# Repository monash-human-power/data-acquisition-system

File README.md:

T2 VCU Data Acquisition System
This repository contains the Raspberry Pi Vehicle Control Unit (VCU) software used by Monash Human Power T2.
The VCU currently performs two main tasks:
Reads vehicle sensor data.
Streams camera footage and telemetry to the rider phone.
The camera and telemetry pipelines are intentionally kept separate. SPI support has been added as an independent hardware communication layer and is used by the ADS131M08 strain gauge sensor.
---
Current System Architecture
```text

                         Raspberry Pi 5 VCU

                                |

              +-----------------+-----------------+

              |                                   |

              |                                   |

         Camera Pipeline                   Telemetry Pipeline

              |                                   |

         Camera.cpp                        VCUController

              |                                   |

         rpicam-vid                         SensorManager

              |                                   |

           FFmpeg                              Sensors

              |                                   |

          MediaMTX                         SensorReading

              |                                   |

            RTSP                           DataSerialiser

              |                                   |

              |                           CommunicationManager

              |                                   |

              +---------------+-------------------+

                              |

                         Ethernet link

                              |

                        Android Phone

```
The Raspberry Pi uses the fixed Ethernet address:
```text

10.55.0.1

```
The Android phone currently uses:
```text

10.55.0.2

```
---
Program Startup
The program begins in:
```text

src/main.cpp

```
`main.cpp` is responsible for starting the camera system and starting the main VCU controller.
The basic startup flow is:
```text

main()

 |

 +--> Register SIGINT handler

 |

 +--> Create Camera

 |

 +--> Camera::startStream()

 |

 +--> Create VCUController

 |

 +--> VCUController::run()

```
The camera and sensor systems then run alongside each other.
Pressing:
```text

Ctrl+C

```
stops the camera stream before the VCU exits.
---
Camera Pipeline
The camera system is intentionally separate from the sensor telemetry system.
The current pipeline is:
```text

Pi Camera

   |

   v

Camera.cpp

   |

   v

rpicam-vid

   |

   v

FFmpeg

   |

   v

MediaMTX

   |

   v

RTSP

   |

   v

Android Phone

```
The current camera stream is available at:
```text

rtsp://10.55.0.1:8554/cam1

```
The camera implementation is contained in:
```text

src/sensors/Camera.h

src/sensors/Camera.cpp

```
Changes to telemetry should not require changes to the camera pipeline.
---
VCU Controller
The main VCU logic is handled by:
```text

src/core/VCUController.h

src/core/VCUController.cpp

```
When `VCUController::run()` starts, it first calls:
```cpp

setup();

```
The setup process currently:
```text

Initialise CommunicationManager

        |

        v

Create I2C bus

/dev/i2c-1

        |

        v

Create GyroscopeSensor

        |

        v

Add sensor to SensorManager

        |

        v

Initialise sensors

        |

        v

Calibrate gyroscope

        |

        v

Start main VCU loop

```
---
Main Sensor Loop
Once setup has completed, the VCU continuously performs:
```text

SensorManager::readAll()

        |

        v

SensorManager::getReadings()

        |

        v

vector<SensorReading>

        |

        v

DataSerialiser::toJSON()

        |

        v

vector<string>

        |

        v

CommunicationManager::sendMessages()

        |

        v

Phone

```
The loop then sleeps according to:
```cpp

config.getSensorReadIntervalMs()

```
before reading the sensors again.
The high-level loop is:
```cpp

while (running)

{

    sensorManager.readAll();

    std::vector<SensorReading> readings =

        sensorManager.getReadings();

    std::vector<std::string> messages =

        DataSerialiser::toJSON(readings);

    communicationManager.sendMessages(messages);

    // Wait until next sensor sample

}

```
---
Sensors
All sensors inherit from:
```text

SensorBase

```
defined in:
```text

src/sensors/Sensor.h

```
A sensor is responsible for:
```text

Initialising hardware

Reading hardware

Updating its SensorReading

```
A sensor should NOT be responsible for:
```text

JSON formatting

TCP networking

Phone communication

```
Those responsibilities belong to `DataSerialiser` and `CommunicationManager`.
---
SensorReading
Sensor data is passed through the system using:
```text

src/data/SensorReading.h

```
The current generic structure is:
```cpp

struct SensorReading

{

    std::string sensorID;

    std::uint64_t timestamp;

    std::unordered_map<std::string, float> values;

    bool isValid;

};

```
The `values` map allows different sensors to provide different measurements without changing the common VCU architecture.
For example, the gyroscope currently produces:
```text

accel_x

accel_y

accel_z

gyro_x

gyro_y

gyro_z

temperature_c

```
A future wheel-speed sensor could simply provide:
```text

speed_kmh

```
without requiring a different `SensorReading` structure.
---
Gyroscope
The currently implemented sensor is an MPU6050.
Files:
```text

src/sensors/GyroscopeSensor.h

src/sensors/GyroscopeSensor.cpp

```
It is currently connected directly to:
```text

/dev/i2c-1

```
with I2C address:
```text

0x68

```
The sensor reads:
```text

Accelerometer X

Accelerometer Y

Accelerometer Z

Gyroscope X

Gyroscope Y

Gyroscope Z

Temperature

```
During VCU startup, the gyroscope is calibrated.
The bike/gyro should remain still while the following message is displayed:
```text

Keep gyroscope still for calibration...

```
---
SensorManager
Files:
```text

src/core/SensorManager.h

src/core/SensorManager.cpp

```
`SensorManager` owns the collection of sensors.
Its main responsibilities are:
```text

addSensor()

initAll()

readAll()

getReadings()

getSensorCount()

```
`readAll()` asks every registered sensor to update its latest reading.
`getReadings()` then collects the latest `SensorReading` from every sensor.
This means additional sensors should generally only need to:
Implement the `SensorBase` interface.
Be added to `SensorManager` during VCU setup.
---
DataSerialiser
Files:
```text

src/data/DataSerialiser.h

src/data/DataSerialiser.cpp

```
`DataSerialiser` is responsible for converting `SensorReading` objects into JSON.
Sensors should not manually create JSON.
Example gyroscope packet:
```json

{

  "sensor": "gyro_1",

  "timestamp": 1791119904187,

  "values": {

    "temperature_c": 18.2506,

    "gyro_z": -0.106794,

    "gyro_y": 0.194046,

    "accel_z": 0.506104,

    "gyro_x": -0.0588548,

    "accel_y": 0.377686,

    "accel_x": -0.753418

  },

  "valid": true

}

```
The order of entries inside `values` should not be relied upon.
JSON object field order is not significant.
---
CommunicationManager
Files:
```text

src/communication/CommunicationManager.h

src/communication/CommunicationManager.cpp

```
`CommunicationManager` handles communication between the VCU and phone.
The current telemetry system runs a TCP server on:
```text

10.55.0.1:9001

```
The phone acts as the TCP client.
The data path is:
```text

VCU

 |

 | JSON over TCP

 v

10.55.0.1:9001

 |

 | Ethernet

 v

Android Phone

```
Each telemetry message is sent as JSON.
The telemetry connection is separate from the RTSP camera connection.
Therefore the phone receives:
```text

Camera:

rtsp://10.55.0.1:8554/cam1

Telemetry:

TCP 10.55.0.1:9001

```
---
Testing Telemetry Locally
Start the VCU:
```bash

./vcu

```
The output should include:
```text

Telemetry server ready on port 9001

Phone should connect to 10.55.0.1:9001

```
In another terminal on the Pi, connect using netcat:
```bash

nc 127.0.0.1 9001

```
You should receive JSON packets such as:
```json

{"sensor":"gyro_1","timestamp":1791119904187,"values":{"temperature_c":18.2506,"gyro_z":-0.106794,"gyro_y":0.194046,"accel_z":0.506104,"gyro_x":-0.0588548,"accel_y":0.377686,"accel_x":-0.753418},"valid":true}

```
Press:
```text

Ctrl+C

```
to exit netcat.
---
SPI Communication (New — Hardware Layer)
The VCU now includes a reusable SPI bus implementation in addition to the existing I2C bus. It is used by the ADS131M08 strain gauge sensor described below.
Files
```text
src/hardware/SPIBus.h
src/hardware/SPIBus.cpp
tests/test_spi.cpp
```
`SPIBus` functionality
`openBus()` — opens a Linux `spidev` device and configures its SPI mode, bits per word and clock speed.
`closeBus()` — closes the file descriptor.
`transfer(tx, rx)` — performs a full-duplex SPI transfer: transmit and receive happen together.
`write(data)` — sends bytes while discarding received bytes.
`isOpen()` — reports whether the device is open.
The default constructor settings are:
```cpp
SPIBus spi("/dev/spidev0.0", 1000000, 0);
```
These specify device `/dev/spidev0.0`, a 1 MHz clock, and SPI mode 0. Settings may need changing for a particular sensor. The Linux SPI interface is accessed through `ioctl()` and `<linux/spi/spidev.h>`.
Compile SPI test
From the repository root, on Linux or WSL with the Linux SPI headers available:
```bash
g++ -std=c++17 tests/test_spi.cpp src/hardware/SPIBus.cpp -Isrc -o test_spi
```
Run the test on a Raspberry Pi with SPI enabled:
```bash
./test_spi
```
To check whether a Raspberry Pi exposes SPI devices:
```bash
ls /dev/spidev*
```
If needed, enable SPI under `sudo raspi-config` → Interface Options → SPI. Device names may vary with configuration.
Test status: The SPI code has been compiled with C++17 in WSL. A successful compile confirms source-level buildability, not successful communication with an SPI peripheral. WSL usually has no `/dev/spidev0.0`, and even a successful transfer on a Pi without a connected peripheral does not validate sensor data.
Adding SPI sensors
SPI sensors inherit from `SPISensor` (`src/sensors/SPISensor.h`), which holds a reference to a shared `SPIBus`. Implement a sensor-specific driver that writes a `SensorReading` and register it with `SensorManager` during `VCUController::setup()`. The existing `DataSerialiser` → `CommunicationManager` → phone telemetry path should remain unchanged. The camera pipeline is also unaffected.
`openBus()`, `transfer()` and `isOpen()` are virtual so that tests can replace the bus with a simulated device.
---
Strain Gauges (ADS131M08 over SPI)
Full Wheatstone bridge strain gauges are read through a TI ADS131M08 8-channel, 24-bit ADC.
Files
```text
src/hardware/ADS131M08.h
src/hardware/ADS131M08.cpp
src/hardware/GPIOInput.h
src/hardware/GPIOInput.cpp
src/sensors/SPISensor.h
src/sensors/SPISensor.cpp
src/sensors/analog/StrainGaugeSensor.h
src/sensors/analog/StrainGaugeSensor.cpp
tests/test_strain_gauge.cpp
```
`ADS131M08` is the chip driver: frame building, RESET/RREG/WREG/NULL commands, PGA gain, oversampling ratio, global chop and output CRC checking. `StrainGaugeSensor` turns bridge voltages into strain. `GPIOInput` watches the ADC's DRDY pin for falling edges using the Linux GPIO character device (`/dev/gpiochipN`), so no extra library is needed.
SPI settings
The ADS131M08 uses SPI mode 1 (CPOL = 0, CPHA = 1), not the `SPIBus` default of mode 0. `VCUController` opens `/dev/spidev0.0` at 1 MHz in mode 1 (see `SystemConfig`). Frames are 10 words of 24 bits (30 bytes): a response word, eight channel words and a CRC word.
Hardware requirements
CLKIN is driven by the on-board SiT1602BC-21-25E-4.096000G oscillator (4.096 MHz, 2.5 V). This frequency is set by `StrainGaugeADCSettings::clockHz`, so change it there if the oscillator changes. The output data rate is (CLKIN / 2) / OSR:
```text
OSR     Data rate at 4.096 MHz
1024    2000 SPS
2048    1000 SPS
4096     500 SPS   (default)
8192     250 SPS
16256    126 SPS
```
The datasheet specifies low-power mode (CLOCK PWR = 01) at a 4.096 MHz CLKIN, so that is the default (`StrainGaugeADCSettings::powerMode`). The crystal oscillator circuit is turned off (XTAL_DIS) because CLKIN is driven by the external oscillator. With the default 8 samples per reading, each `read()` takes about 16 ms. The SYNC/RESET pin must be held high. If CLKIN is missing, the ADC still answers commands but never produces data, and initialisation fails with `timed out waiting for ADS131M08 data (check CLKIN)`.
Voltage reference
AVDD and DVDD are both 3.3 V. The ADS131M08 has no AVSS pin: AGND (0 V) is its negative supply. REFIN is driven to 1.25 V by a 10k/10k divider (R9/R12) from the 2.5 V rail, so the driver sets EXTREF_EN (CLOCK bit 6) to use it as the reference. The ADC then uses 0.96 × REFIN = 1.2 V, which gives a full-scale range of ±1.2 V / gain. These are the defaults in `StrainGaugeADCSettings` (`externalReference`, `refinVolts`).
EXTREF_EN is defined in the CLOCK register description (datasheet Table 8-17), although the summary register map (Table 8-12) shows it as reserved. The driver therefore reads CLOCK back. If the bit did not set, it prints `warning: EXTREF_EN did not set, using the internal 1.2 V reference`. Readings are still correct in that case, but no longer ratiometric. The startup line says which reference is in use.
The bridges are excited from the same 2.5 V rail, so the measurement is ratiometric: a low or noisy rail scales the bridge output and the reference together, so the strain value is unaffected.
Wiring to the Pi (via the VCU HAT)
The strain gauge board's J3 connects to J8 on the VCU HAT, which sits on the Pi's GPIO header. The HAT passes SCLK, MOSI, MISO and the chip selects through an ISO7761 digital isolator. The cable must be wired pin 1 to pin 1.
```text
ADC board J3   HAT J8      Path on the HAT              Pi 5 header
1  3.3 V       1  3V3      HAT 3V3 rail                 -
2  GND         2  GND      GND                          GND
3  SCLK        3  ISO-SCLK ISO7761 OUTC <- INC          pin 23 (GPIO 11)
4  DIN         4  ISO-MOSI ISO7761 OUTD <- IND          pin 19 (GPIO 10)
5  DOUT        5  ISO-MISO ISO7761 INF  -> OUTF         pin 21 (GPIO 9)
6  CS          6  ISO-CE0  ISO7761 OUTB <- INB          pin 24 (GPIO 8, CE0) -> /dev/spidev0.0
7  DRDY        7  ISO-INT0 (not through the isolator)   pin 18 (GPIO 24)
8  GND         8  GND      GND                          GND
```
ISO-CE0 has a 10k pull-up (R20), so the ADC stays deselected while the Pi is booting. HAT connector J9 is the same but uses CE1 (`/dev/spidev0.1`) and INT1 on pin 22 (GPIO 25), for a second SPI board.
DRDY
The ADC pulls DRDY low when a new conversion is ready, and DRDY falls again for every conversion even if the last one was not read. The ADC also buffers two samples per channel, so after the gap between VCU loop iterations both are full and old (datasheet 8.5.1.9.1). Each `read()` therefore drops stale DRDY edges, reads two frames to empty the buffer, and then, for each sample, waits for a falling edge on GPIO 24 and reads one SPI frame. Reading straight after DRDY falls also avoids reading while a conversion completes, which the datasheet warns blocks the next DRDY pulse. The GPIO is found by its chip label (`pinctrl-rp1` on the Pi 5) rather than a fixed `/dev/gpiochipN` path, because the number differs between kernel versions. Both the label and the line are set in `SystemConfig`.
If the GPIO cannot be opened, the sensor prints `warning: DRDY pin unavailable, polling STATUS instead` and keeps working by polling the STATUS register over SPI. The user running `./vcu` must be in the `gpio` group (and the `spi` group for `/dev/spidev0.0`), which the default Pi OS user already is. To check the pin from the shell, run `gpioinfo | grep -A30 pinctrl-rp1` (from the `gpiod` package) and look for line 24.
The isolator adds a delay to each signal, and MISO pays it twice: the clock goes out through the isolator and the data comes back through it. This has no effect at the default 1 MHz SCLK, but keep it in mind before raising `spiSpeedHz` far.
SYNC/RESET is pulled up to 3.3 V on the board through R19.
Hardware checks against the datasheet (SBAS950B, `adc_datasheet.pdf`)
- CLKIN level (out of spec): CLKIN is a digital input with VIH = 0.8 × DVDD = 2.64 V at DVDD = 3.3 V. The SiT1602BC-21-25E oscillator runs from 2.5 V, so its high level is at most 2.5 V. It may work on the bench, but it is below the guaranteed threshold. Use the 3.3 V version (SiT1602BC-21-33E-4.096000G) or power the oscillator from 3.3 V if the part allows it.
- Input voltage range: at gains of 8 to 128, each input must stay between AGND − 1.3 V and AVDD − 1.8 V (1.5 V at AVDD = 3.3 V). A bridge excited at 2.5 V sits at about 1.25 V, which is within range. A bridge excited at 3.3 V (about 1.65 V) would not be.
- REFIN: 1.1 V to 1.3 V, nominal 1.25 V. The full-scale range keeps the 1.2 : 1.25 ratio, which is the 0.96 factor used in the code.
- CLKIN frequency: 0.3 to 4.15 MHz in low-power mode, so 4.096 MHz is within range.
- CAP 220 nF, AVDD and DVDD 1 µF: matches the strain gauge board.
Raspberry Pi 5 setup
Enable SPI with `sudo raspi-config` → Interface Options → SPI, or add `dtparam=spi=on` to `/boot/firmware/config.txt`, then reboot. Check that `/dev/spidev0.0` exists (`ls /dev/spidev*`). This is SPI0 with chip select CE0, which the HAT routes to J8. If the strain gauge board is moved to J9 (CE1), change `spiDevicePath` in `SystemConfig` to `/dev/spidev0.1`.
Channel configuration
Each bridge is described by a `StrainChannelConfig`:
```cpp
StrainChannelConfig bridge0;
bridge0.name = "strain_0";        // telemetry key prefix
bridge0.channel = 0;              // AIN0P / AIN0N
bridge0.gaugeFactor = 2.1f;       // value on the gauge packet (spec 2.0-2.2)
bridge0.bridgeFactor = 1.0f;      // 1.0 for 4 active gauges
bridge0.excitationVoltage = 2.5f; // bridge excitation (2.5 V rail)
bridge0.pgaGain = 32;             // input range +/- 1.2 V / gain
```
Strain is calculated as:
```text
strain = (Vout - Vout_at_tare) / Vex / (gaugeFactor * bridgeFactor)
```
Use `bridgeFactor = (1 + poisson) / 2` for a full bridge with two axial and two Poisson gauges. A negative `bridgeFactor` flips the sign if the bridge is wired the other way round.
Choose the PGA gain so the largest expected bridge output, plus any bridge imbalance, stays inside +/- 1.2 V / gain. For example, 1000 microstrain with GF 2.0 and 2.5 V excitation gives 5 mV, which fits at gain 64 (+/- 18.75 mV) or gain 128 (+/- 9.375 mV).
Up to eight bridges can be read by one sensor by passing several `StrainChannelConfig` entries.
Startup and readings
During `VCUController::setup()` the sensor resets the ADC, checks the ID register, configures it, and then tares. The structure must be unloaded while this message is displayed:
```text
Keep strain gauges unloaded for taring...
```
Each `read()` averages 8 fresh conversions per channel and produces, for each bridge:
```text
<name>_microstrain
<name>_mv           raw bridge output before taring
```
Example packet:
```json
{"sensor":"strain_1","timestamp":1791119904187,"values":{"strain_0_microstrain":512.4,"strain_0_mv":4.62},"valid":true}
```
Settings shared by all channels (oversampling, samples per reading, global chop, clock frequency and reference) are passed as a `StrainGaugeADCSettings`, whose defaults match the strain gauge PCB.
`valid` is false if any configured input is saturated. If that happens, lower the PGA gain.
Strain gauge test
`tests/test_strain_gauge.cpp` checks the driver and strain maths against a simulated ADS131M08, so it runs on any Linux machine without hardware:
```bash
g++ -std=c++17 tests/test_strain_gauge.cpp src/hardware/SPIBus.cpp src/hardware/GPIOInput.cpp src/hardware/ADS131M08.cpp src/sensors/SPISensor.cpp src/sensors/analog/StrainGaugeSensor.cpp -Isrc -Isrc/hardware -Isrc/sensors -Isrc/sensors/analog -o test_strain_gauge
./test_strain_gauge
```
Test status: the strain gauge code passes the simulated-device test but has not yet been run against a real ADS131M08.
---
Adding a New Sensor
When adding another sensor, preserve the current architecture:
```text

Hardware

   |

   v

Sensor subclass

   |

   v

SensorReading

   |

   v

SensorManager

   |

   v

DataSerialiser

   |

   v

CommunicationManager

   |

   v

Phone

```
A new sensor should:
Inherit from `SensorBase` or the appropriate sensor subclass.
Implement `init()`.
Implement `read()`.
Store measurements inside `lastReading.values`.
Set `lastReading.timestamp`.
Set `lastReading.isValid`.
Be registered with `SensorManager`.
Do not add networking code directly to a sensor.
Do not add JSON formatting directly to a sensor.
---
Source Structure
```text

src/

├── communication/

│   ├── CommunicationManager.cpp

│   └── CommunicationManager.h

│

├── config/

│   ├── SystemConfig.cpp

│   └── SystemConfig.h

│

├── core/

│   ├── SensorManager.cpp

│   ├── SensorManager.h

│   ├── VCUController.cpp

│   └── VCUController.h

│

├── data/

│   ├── DataSerialiser.cpp

│   ├── DataSerialiser.h

│   ├── SensorReading.cpp

│   └── SensorReading.h

│

├── hardware/

│   ├── ADS131M08.cpp
│   ├── ADS131M08.h
│   ├── I2CBus.cpp

│   ├── I2CBus.h
│   ├── SPIBus.cpp
│   └── SPIBus.h

│

├── sensors/

│   ├── Camera.cpp

│   ├── Camera.h

│   ├── GyroscopeSensor.cpp

│   ├── GyroscopeSensor.h

│   ├── I2CSensor.cpp

│   ├── I2CSensor.h

│   ├── Sensor.h

│   └── ...

│

└── main.cpp

```
---
Building the VCU
From the repository root:
```bash

g++ -std=c++17 src/main.cpp src/core/VCUController.cpp src/core/SensorManager.cpp src/config/SystemConfig.cpp src/communication/CommunicationManager.cpp src/data/DataSerialiser.cpp src/data/SensorReading.cpp src/hardware/I2CBus.cpp src/hardware/SPIBus.cpp src/hardware/GPIOInput.cpp src/hardware/ADS131M08.cpp src/sensors/I2CSensor.cpp src/sensors/SPISensor.cpp src/sensors/GyroscopeSensor.cpp src/sensors/analog/StrainGaugeSensor.cpp src/sensors/Camera.cpp -I. -Isrc -Isrc/core -Isrc/config -Isrc/communication -Isrc/data -Isrc/hardware -Isrc/sensors -Isrc/sensors/i2c -Isrc/sensors/analog -Isrc/util -pthread -o vcu

```
Run with:
```bash

./vcu

```
Stop with:
```text

Ctrl+C

```

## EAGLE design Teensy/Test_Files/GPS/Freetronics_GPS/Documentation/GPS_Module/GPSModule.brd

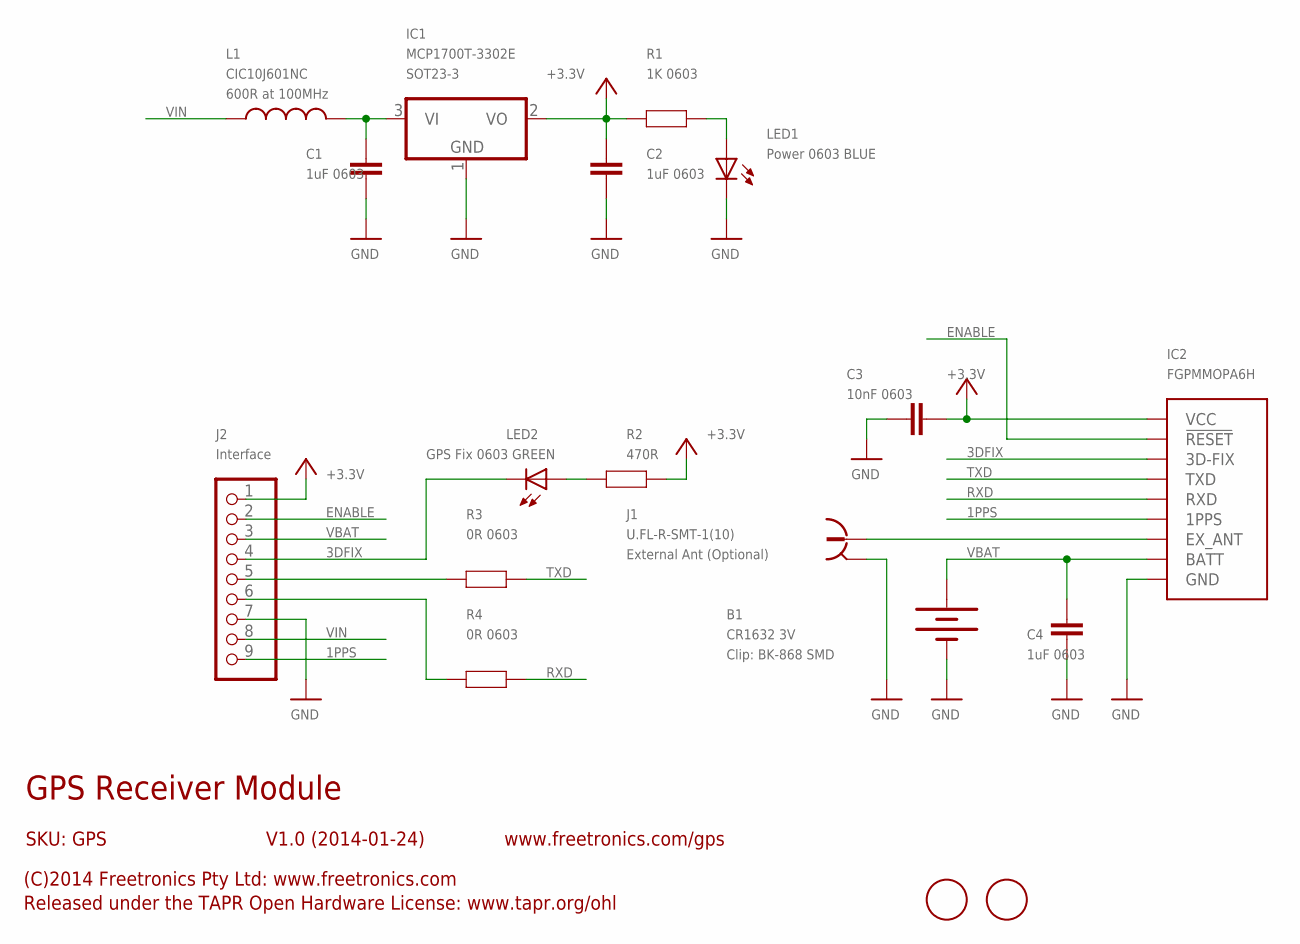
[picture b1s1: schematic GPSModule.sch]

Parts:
B1: CR1632 3V; BATCON_16MM
C1, C2, C4: 1uF 0603; 0603
C3: 10nF 0603; 0603
FD1, FD2: FIDUCIAL; FIDUCIAL_1MM
IC1: MCP1700T-3302E; SOT23
IC2: FGPMMOPA6H; GPS
J1: U.FL-R-SMT-1(10); UFL
J2: Interface; 1X09
L1: 600R at 100MHz; 0603
LED1: Power 0603 BLUE; LED-0603
LED2: GPS Fix 0603 GREEN; LED-0603
R1: 1K 0603; 0603
R2: 470R; 0603
R3, R4: 0R 0603; 0603

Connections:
1PPS: IC2.13 (1PPS), J2.9
3DFIX: IC2.5 (3D-FIX), J2.4, LED2.C
+3V3: C2.2, C3.1, IC1.2 (VO), IC2.1 (VCC), J2.1, R1.2, R2.1
ENABLE: IC2.2 (!RESET), J2.2
GND: B1.GND (-), C1.1, C2.1, C3.2, C4.1, IC1.1 (GND), IC2.3 (GND), IC2.8 (GND), IC2.12 (GND), IC2.19 (GND), J1.GND, J1.GND@1 (GND), J2.7, LED1.C
unnamed: J2.5, R3.2
unnamed: IC2.11 (EX_ANT), J1.SIG
unnamed: LED1.A, R1.1
unnamed: LED2.A, R2.2
unnamed: C1.2, IC1.3 (VI), L1.2
unnamed: J2.6, R4.2
RXD: IC2.10 (RXD), R4.1
TXD: IC2.9 (TXD), R3.1
VBAT: B1.PWR@1 (+), C4.2, IC2.4 (BATT), J2.3
VIN: J2.8, L1.1

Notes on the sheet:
GPS Receiver Module
V1.0 (2014-01-24)
SKU: GPS
(C)2014 Freetronics Pty Ltd: www.freetronics.com
Released under the TAPR Open Hardware License: www.tapr.org/ohl
www.freetronics.com/gps

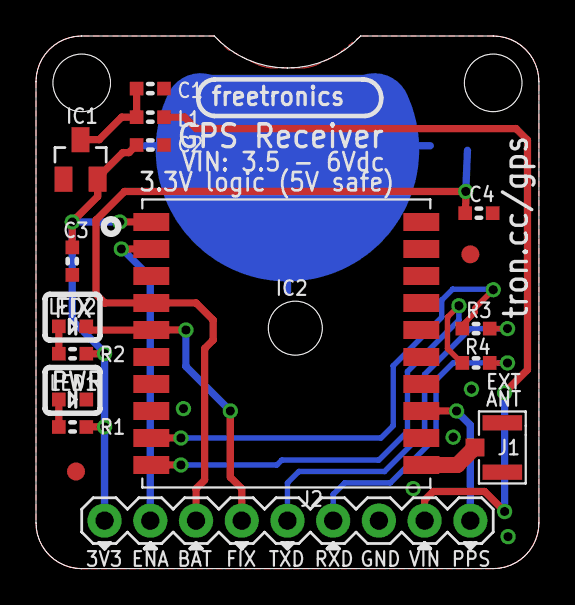
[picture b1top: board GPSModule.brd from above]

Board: 2 copper layers, 27.9 x 29.6 mm, 18 parts (1 on the bottom side), 15 nets.

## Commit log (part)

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2022-01-31 Add ant-plus service
2022-01-31 Update READMEs
2022-02-01 Add python-dotenv dependency
2022-02-02 Add ANT+ service (#83)
2022-02-06 Bump lodash from 4.17.19 to 4.17.21 in /ant_plus_sensor (#74)
2022-02-06 Bump numpy from 1.18.4 to 1.21.0 in /utils
    Bumps [numpy](https://github.com/numpy/numpy) from 1.18.4 to 1.21.0.
    - [Release notes](https://github.com/numpy/numpy/releases)
    - [Changelog](https://github.com/numpy/numpy/blob/main/doc/HOWTO_RELEASE.rst.txt)
    - [Commits](https://github.com/numpy/numpy/compare/v1.18.4...v1.21.0)
    ---
    updated-dependencies:
2022-02-06 Add .env.example file
2022-02-06 Fix file directory name in install script
2022-02-11 Document ant+ permissions requirements
2022-03-06 Update fake WM script to use Wm online status topic
2022-03-30 update: readme
2022-04-03 docs: simplify DAS readme
    - add table of contents
    - simplify install to 2 commands and a single command to run tests
2022-04-06 fix: remove old travis file
    This file is no longer needed as travis is not used as a CICD platform, GitHub actions are.
2022-04-06 Bump ajv from 6.10.2 to 6.12.6 in /ant_plus_sensor (#89)
    Bumps [ajv](https://github.com/ajv-validator/ajv) from 6.10.2 to 6.12.6.
    - [Release notes](https://github.com/ajv-validator/ajv/releases)
    - [Commits](https://github.com/ajv-validator/ajv/compare/v6.10.2...v6.12.6)
    ---
    updated-dependencies:
    - dependency-name: ajv
2022-04-06 docs: simplify DAS readme (#93)
    * docs: simplify DAS readme
    - add table of contents
    - simplify install to 2 commands and a single command to run tests
    * docs: add optional `poetry shell`
2022-04-06 feat: add dev container
2022-04-07 Fix speed sensor not getting detected
2022-04-07 Connect/read ant plus speed sensor (untested)
2022-04-07 Disable reed switch on back WM
2022-04-12 Wait before starting ant+ service
2022-04-13 fix: change logger to mqtt-logger package
2022-04-13 add mqtt-logger package
2022-04-13 refactor: format `das_data_generator`
2022-04-13 Use 'voltage' keyword for battery topic
2022-04-14 Add systemd servicee file for raw MQTT logger
2022-05-17 fix: do not write out excel tabs if no data is found (#100)
2022-05-18 Bump lodash from 4.17.19 to 4.17.21 in /ant_plus_sensor (#97)
    Bumps [lodash](https://github.com/lodash/lodash) from 4.17.19 to 4.17.21.
    - [Release notes](https://github.com/lodash/lodash/releases)
    - [Commits](https://github.com/lodash/lodash/compare/4.17.19...4.17.21)
    ---
    updated-dependencies:
    - dependency-name: lodash
2022-06-22 Bump numpy from 1.21.0 to 1.22.0 in /utils
    Bumps [numpy](https://github.com/numpy/numpy) from 1.21.0 to 1.22.0.
    - [Release notes](https://github.com/numpy/numpy/releases)
    - [Changelog](https://github.com/numpy/numpy/blob/main/doc/HOWTO_RELEASE.rst)
    - [Commits](https://github.com/numpy/numpy/compare/v1.21.0...v1.22.0)
    ---
    updated-dependencies:
2022-08-09 Implement v3 start topic in wireless modules (untested).
2022-08-22 add basic crash detection functions to mpu_sensor.py
2022-08-22 Remove redundant lines of code
2022-09-04 Remove redundant output statement
2022-09-06 Bump numpy from 1.21.0 to 1.22.0 in /utils (#102)
    Bumps [numpy](https://github.com/numpy/numpy) from 1.21.0 to 1.22.0.
    - [Release notes](https://github.com/numpy/numpy/releases)
    - [Changelog](https://github.com/numpy/numpy/blob/main/doc/HOWTO_RELEASE.rst)
    - [Commits](https://github.com/numpy/numpy/compare/v1.21.0...v1.22.0)
    ---
    updated-dependencies:
2022-09-15 add crash alert system
2022-09-17 Change LED mode depending on start message value
2022-09-26 add base class for raspberry pi based sensor
2022-09-26 add class for raspberry pi based wireless module
2022-09-27 update poetry files
2022-09-27 fix issues with mqtt
2022-09-27 move message sending files to a separate package
2022-09-27 add slack webhook parameter to class calls
2022-10-04 add some documentation
2022-10-04 add crash alert service file
2022-10-10 Downgrade python version requirement (#107)
    * Update V3 fake module script to use new V3 start topics
    * Downgrade python requirement to py3.7
2022-10-10 Bump glob-parent and mqtt in /ant_plus_sensor
    Bumps [glob-parent](https://github.com/gulpjs/glob-parent) to 5.1.2 and updates ancestor dependency [mqtt](https://github.com/mqttjs/MQTT.js). These dependencies need to be updated together.
    Updates `glob-parent` from 5.1.0 to 5.1.2
    - [Release notes](https://github.com/gulpjs/glob-parent/releases)
    - [Changelog](https://github.com/gulpjs/glob-parent/blob/main/CHANGELOG.md)
    - [Commits](https://github.com/gulpjs/glob-parent/compare/v5.1.0...v5.1.2)
    Updates `mqtt` from 2.18.8 to 4.3.7
2022-10-18 add config.example
2022-11-24 Add code to run MQTT client, still need to test
2022-11-29 Change connection to localhost
2022-11-29 Reformat conversion code to work within the class
2022-12-06 Include functionality to record topic data, currently doesn't work correctly
2022-12-06 update poetry lock file and mhp import
2022-12-07 add quotations in env example file
2022-12-10 Add parsed arguements
2022-12-11 add README.md file to directory
2022-12-14 add MQTT_HOST as a host option
2023-01-05 Create radio interface
2023-01-07 Establish connection to nrf24 module
2023-01-09 Clear DB data each time false is sent
2023-01-10 Have log time be metadata in the file name rather than run number
2023-01-11 Change file naming conventions
2023-01-12 Small changes to logging info
2023-01-12 added module for mpu6500 board
2023-01-13 Remove redundant code and comments from sns_message_sender.py
2023-01-14 Attempt 1 at communication
2023-01-14 Create folder to hold sqlite logs
2023-01-14 Fix small issues and add TODOs
2023-01-15 convert wind data to number
2023-01-15 Format documents
2023-01-16 Writing docstring for logger class
2023-01-16 Added roll and pitch method
2023-01-17 Add more documentation
2023-01-17 More changes to README
2023-01-18 Implement crash alert (#110)
2023-01-18 Bump certifi from 2022.9.24 to 2022.12.7 in /crash_alert
    Bumps [certifi](https://github.com/certifi/python-certifi) from 2022.9.24 to 2022.12.7.
    - [Release notes](https://github.com/certifi/python-certifi/releases)
    - [Commits](https://github.com/certifi/python-certifi/compare/2022.09.24...2022.12.07)
    ---
    updated-dependencies:
    - dependency-name: certifi
2023-01-23 add README
2023-01-23 add setup steps to README
2023-01-23 fix typo
2023-01-27 cleaned up all the comments, print statement and readability
2023-01-28 remove redundant comment
2023-01-28 fixed up commas
2023-01-28 removed config.py and complementary.ipynb
2023-01-30 Live Anemometer Data (#114)
    * add base class for raspberry pi based sensor
    * add wind sensor
    * add class for raspberry pi based wireless module
    * fix issues with mqtt
    * restructure wireless_modules_py folder
    * add comments
2023-01-30 Fixing conflicts in poetry lock
2023-01-30 Get correct file version, accepting current changes
2023-01-30 Put back the config example, shouldn't have been deleted
2023-01-30 accepted incoming requests
2023-02-01 Fix broker address argument logic
2023-02-12 Create service file for log_2_excel.py file
2023-02-12 Get rid of this file
2023-02-24 Add cooldown as a parameter and change default to 120secs (#116)
2023-04-02 Created class and added calibration coefficients
2023-05-05 added main file to the pressure_module
2023-05-08 Added option to change the wiring config used
2023-05-09 updated poetry files and libraries
2023-07-13 added code for fake data to test for module 5 with wind sensor
2023-07-26 Changed bike CE pin, increased power
2023-07-28 Updated wheel circumference (#118)
2023-07-31 valid mock wind data can be published to subscribed powershell test
2023-07-31 Limiting maximum queue length and setting data rate slow again
2023-08-05 increased sample rate and array dumping
2023-08-07 Mock Wind Data (#119)
    * added code for fake data to test for module 5 with wind sensor
    * valid mock wind data can be published to subscribed powershell test
    * Added parameter to reach degrees in greater range
    ---------
2023-08-07 Added strain_gauge topic to banned list
2023-08-10 Added service files for radio bridge
2023-08-14 When a time isn't passed, make the function sleep (#122)
2023-09-06 Combine strain and crash data into one topic, for publishing
2023-09-06 Ensure passed interval value is integer not float
2023-09-08 Making logger only output db files and creating a converter to do manually later
2023-09-09 Arosh heenkenda/logger alterations (#124)
    * Allow parsing of mpu and strain data
    * Making logger only output db files and creating a converter to do manually later
    * Remove annoying whitespace
    ---------
2023-09-09 Parse Strain & MPU Data (#125)
    * Ensure that we actually parse Strain and MPU
    * Oops forgot a comma
    ---------
2023-09-12 Update ANT+ installation instructions (#126)
2023-09-12 Allow wireless module to constantly publish data
2023-09-13 Logging starts only when BOOST starts
2023-09-18 Added python files, converted average.js, provided example usage of new library upon installation
2023-10-02 Fixed bugs in bump strip script, runs together now
2023-10-11 Added MQTT posting to Bump strips and Lap timer
2023-11-21 Files to run DHT22 temp sensor
2023-11-21 Adding wireless module and making small changes to the temp module
2023-11-22 Interpolation looks promising for non strings
2023-11-22 Added help comment to top, fixed time step being fixed
2023-11-27 Changes to the pin on main.py
2023-12-03 Fix context error for config.py and round to 2 dec for print statements
2023-12-16 Set up Poetry to manage all Python dependencies. Moved all Python-related files to a separate package.
2024-01-12 Fixed minor error in connecting to MQTT
2024-01-12 Changed poetry project name to include underscores
2024-02-04 Corrected MQTT unpacking
2024-02-26 Removed code that used initial python library
2024-03-12 Run main and ant connect on separate threads + clean up
2025-02-20 added error handling to I2C read and write and added barometer class
2025-03-31 finish barometer sensor
2025-04-23 accelerometer and gyroscope code done ig
2025-04-24 removing extra empty file
2025-05-09 initialized the GyroSensor.h file for the gyroSensor, as it's no longer gonna be managed by MPU
2025-05-09 renamed the gyro sensor file with the sensor name
2025-07-13 fixed REG_PWR_MGMT0 and REG_GYRO_CONFIG0 data write values
2025-07-15 Josephs/wired module (#129)
    * Initial commit with self-test template
    * added i2c_test project and move wired_module
    * Implement recieving from barometer and transmitting through can bus
    * Implement sending multiple sensors into can bus (gyroscope)
    * Seperate sensor twai messages, convert the float data into an array
    * Enable sending 2 can bus messages at once by removing acceptance filter
2025-07-16 added gyro sensor, placehold wifi and ip values
2025-07-21 Add header files for new SPI class
2025-08-01 Update sensor base header with Arnav's MQTT changes.
2025-08-01 added to setup to get the esp's ip
2025-08-01 testing platform io connection
2025-08-12 The vm code 2.1 folder is the one with the working barometer and mqtt code. Deleted other files to prevent fails. Will gradually debug and test other files from wire_module_arduino and add to this up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
2025-08-25 corrected 2's complement logic
2025-08-25 added actual barometer code to main DPS368
2025-10-13 Add conversion helper functions to temp/humidity file + correct read function
2026-03-25 Added documentation for backlogs and current codebase
2026-05-10 Reset vcu-code for fresh VCU implementation

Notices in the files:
Teensy/Test_Files/GPS/Freetronics_GPS/Documentation/GPS_Module/GPSModule.brd:
(C)2014 Freetronics P/L
